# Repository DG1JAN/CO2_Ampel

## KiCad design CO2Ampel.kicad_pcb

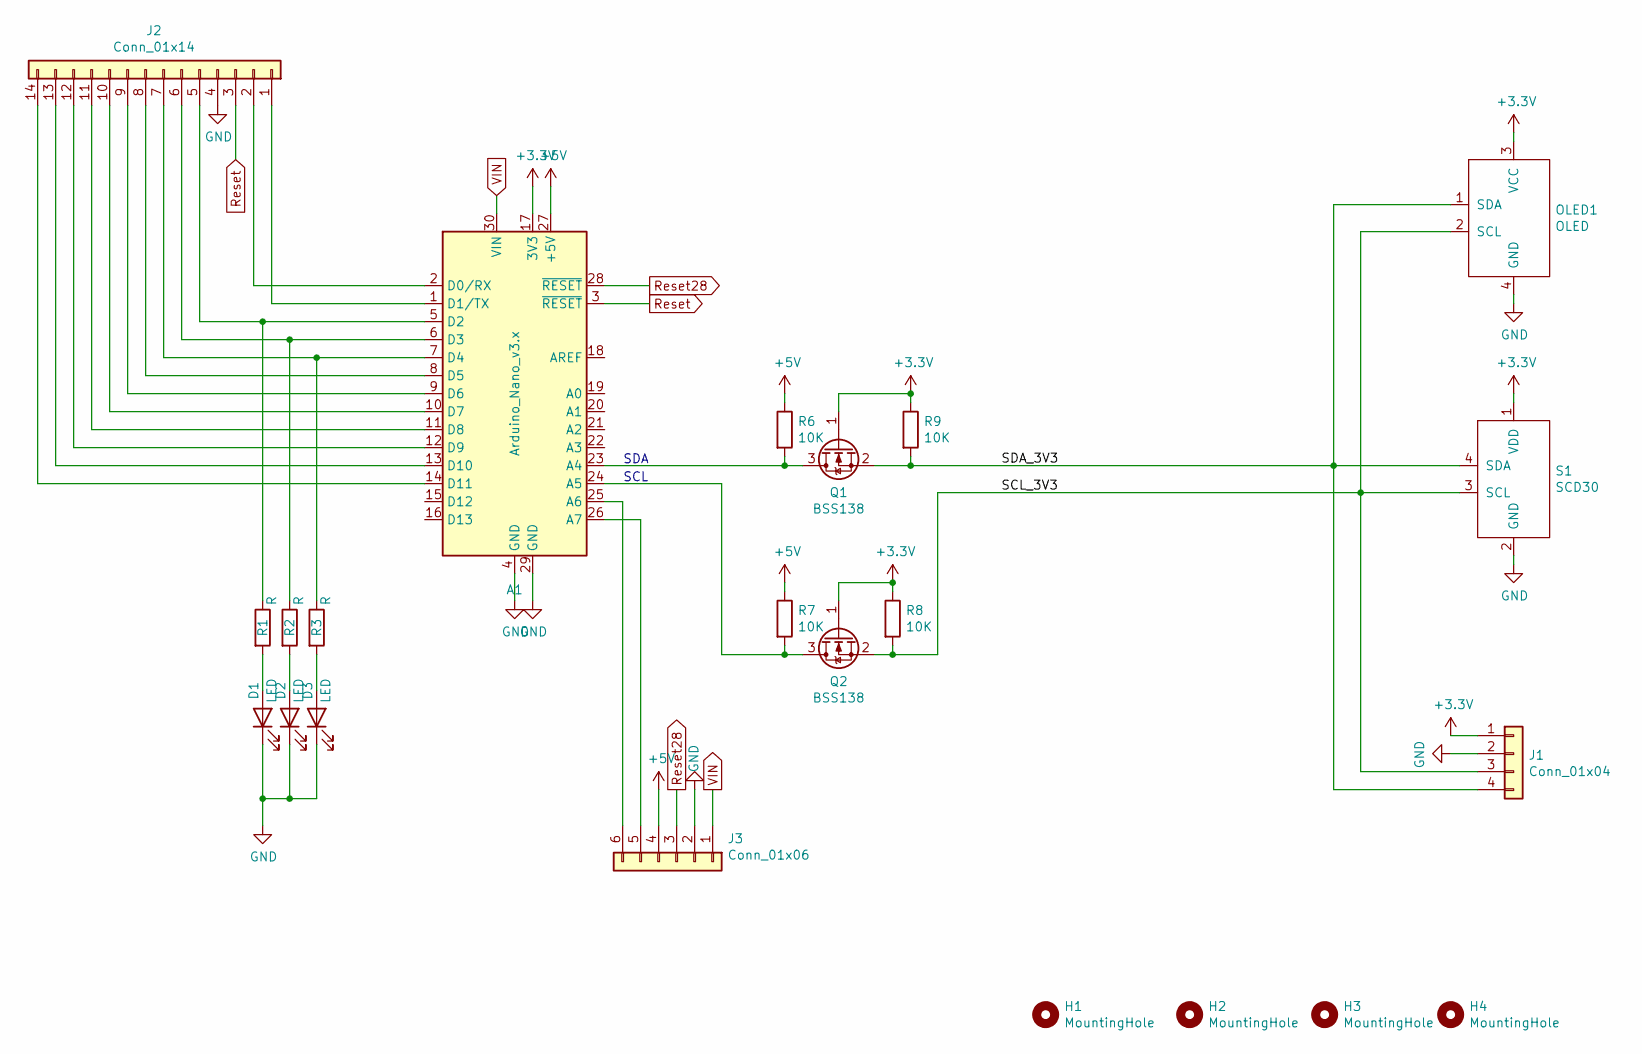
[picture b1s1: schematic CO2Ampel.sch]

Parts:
A1: Arduino_Nano_v3.x; Arduino_Nano
D1, D2, D3: LED; LED_D5.0mm
H1, H2, H3, H4: MountingHole; MountingHole_3.2mm_M3_Pad_TopBottom
J1: Conn_01x04; PinHeader_1x04_P2.54mm_Vertical
J2: Conn_01x14; PinHeader_1x14_P2.54mm_Vertical
J3: Conn_01x06; PinHeader_1x06_P2.54mm_Vertical
OLED1: OLED
Q1, Q2: BSS138; SOT-23
R1, R2, R3: R; R_0603_1608Metric_Pad0.98x0.95mm_HandSolder
R6, R7, R8, R9: 10K; R_0603_1608Metric_Pad0.98x0.95mm_HandSolder
S1: SCD30; scd30

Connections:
+3V3: A1.17 (3V3), J1.1, OLED1.3 (VCC), Q1.1 (G), Q2.1 (G), R8.1, R9.1, S1.1 (VDD)
+5V: A1.27 (+5V), J3.4, R6.1, R7.1
/SCL_3V3: J1.3, OLED1.2 (SCL), Q2.2 (S), R8.2, S1.3 (SCL)
/SDA_3V3: J1.4, OLED1.1 (SDA), Q1.2 (S), R9.2, S1.4 (SDA)
GND: A1.4 (GND), A1.29 (GND), D1.1 (K), D2.1 (K), D3.1 (K), J1.2, J2.4, J3.2, OLED1.4 (GND), S1.2 (GND)
unnamed: A1.1 (D1/TX), J2.1
unnamed: A1.2 (D0/RX), J2.2
unnamed: A1.5 (D2), J2.5, R1.1
unnamed: A1.6 (D3), J2.6, R2.1
unnamed: A1.7 (D4), J2.7, R3.1
unnamed: A1.8 (D5), J2.8
unnamed: A1.9 (D6), J2.9
unnamed: A1.10 (D7), J2.10
unnamed: A1.11 (D8), J2.11
unnamed: A1.12 (D9), J2.12
unnamed: A1.13 (D10), J2.13
unnamed: A1.14 (D11), J2.14
unnamed: A1.23 (A4), Q1.3 (D), R6.2
unnamed: A1.24 (A5), Q2.3 (D), R7.2
unnamed: A1.25 (A6), J3.6
unnamed: A1.26 (A7), J3.5
unnamed: D1.2 (A), R1.2
unnamed: D2.2 (A), R2.2
unnamed: D3.2 (A), R3.2
Reset: A1.3 (~RESET), J2.3
Reset28: A1.28 (~RESET), J3.3
VIN: A1.30 (VIN), J3.1

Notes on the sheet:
SDA
SCL

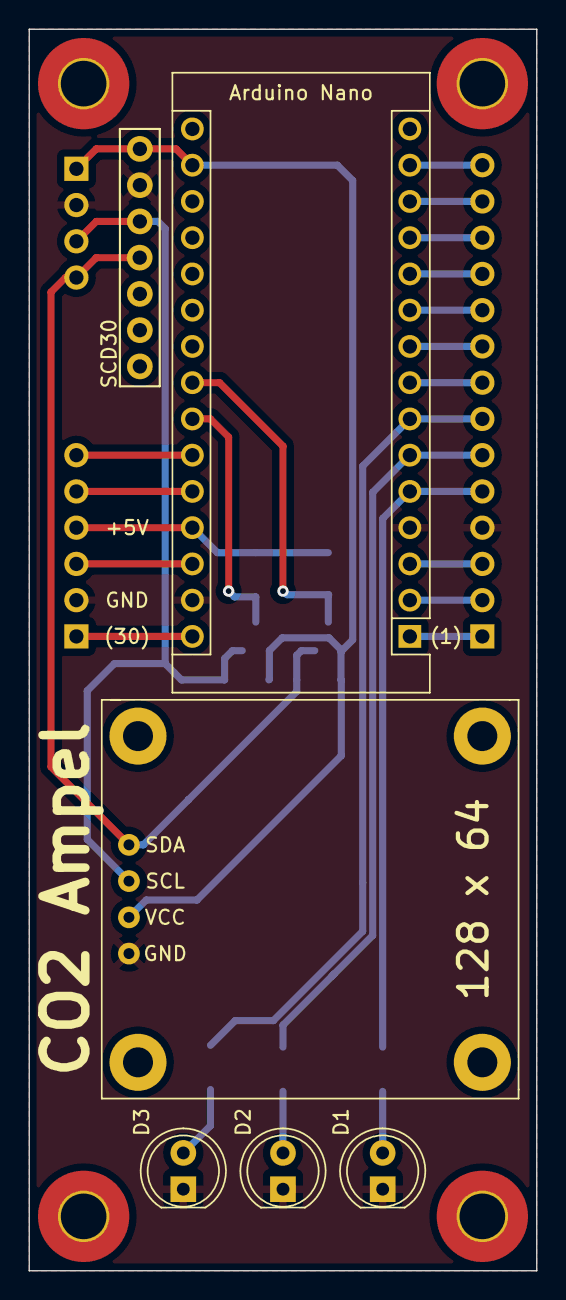
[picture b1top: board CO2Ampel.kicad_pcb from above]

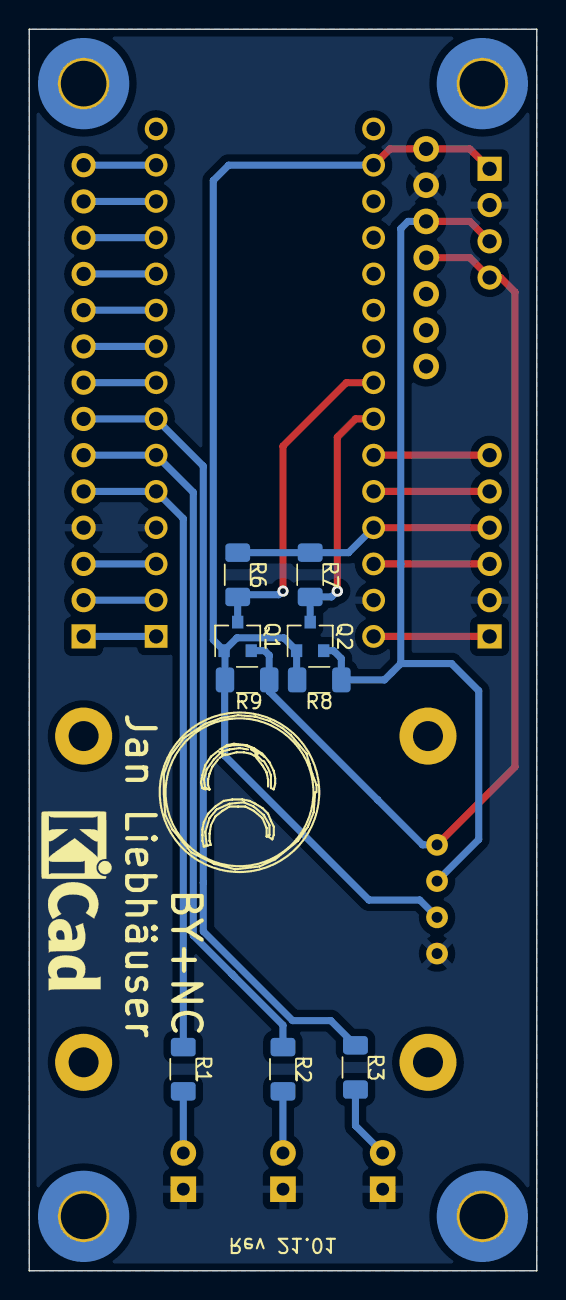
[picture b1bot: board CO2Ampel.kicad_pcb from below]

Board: 2 copper layers, 35.6 x 87.0 mm, 22 parts (10 on the bottom side), 27 nets.
